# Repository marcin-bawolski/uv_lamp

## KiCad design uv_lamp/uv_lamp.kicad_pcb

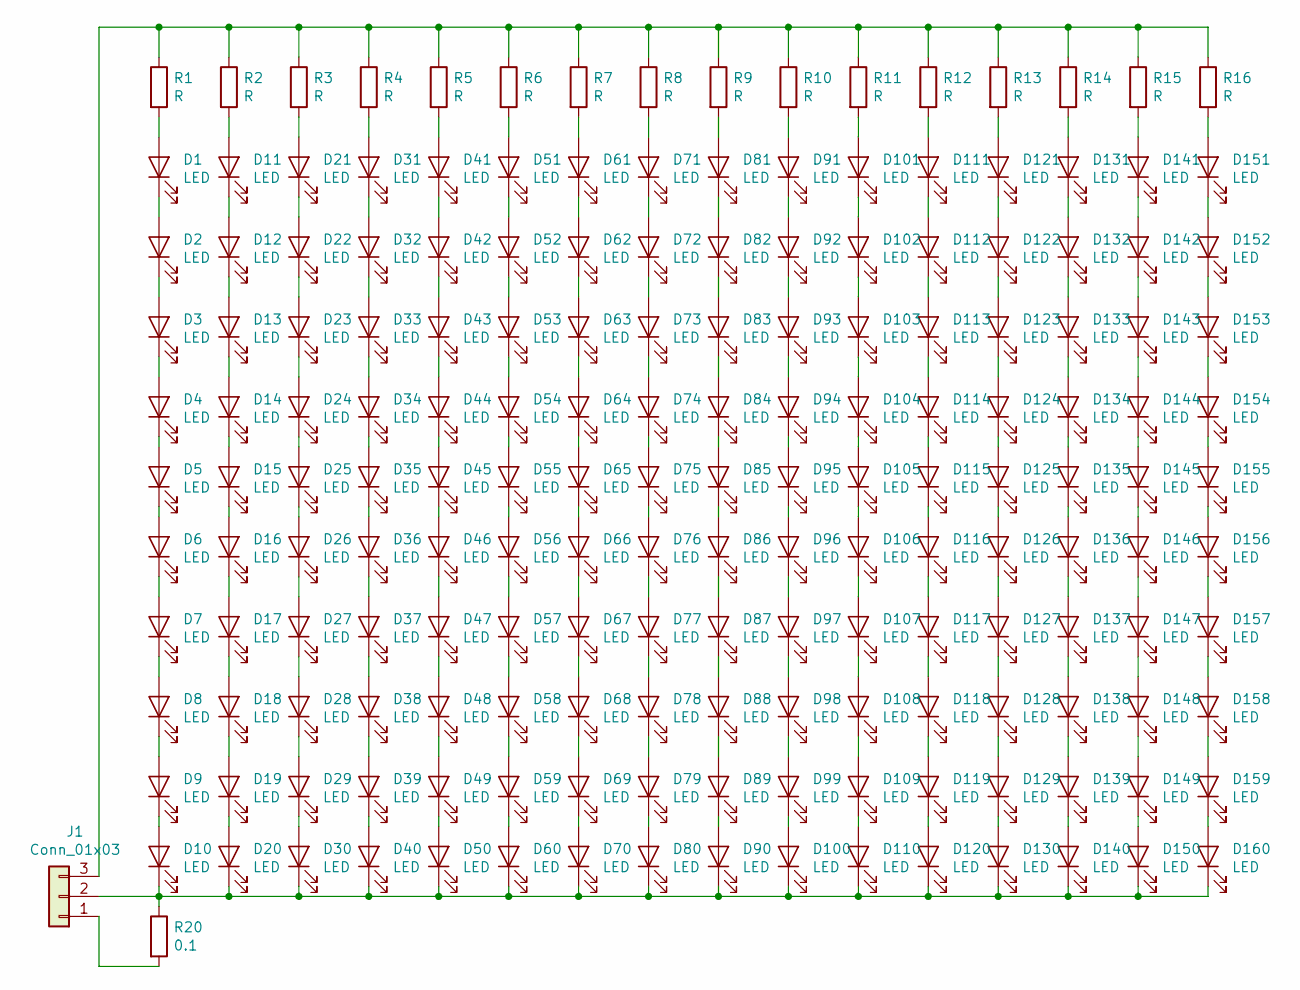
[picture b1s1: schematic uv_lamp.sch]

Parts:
D1, D2, D3, D4, D5, D6, D7, D8, D9, D10, D11, D12, D13, D14, D15, D16, D17, D18, D19, D20, D21, D22, D23, D24, D25, D26, D27, D28, D29, D30, D31, D32, D33, D34, D35, D36, D37, D38, D39, D40, D41, D42, D43, D44, D45, D46, D47, D48, D49, D50, D51, D52, D53, D54, D55, D56, D57, D58, D59, D60, D61, D62, D63, D64, D65, D66, D67, D68, D69, D70, D71, D72, D73, D74, D75, D76, D77, D78, D79, D80, D81, D82, D83, D84, D85, D86, D87, D88, D89, D90, D91, D92, D93, D94, D95, D96, D97, D98, D99, D100, D101, D102, D103, D104, D105, D106, D107, D108, D109, D110, D111, D112, D113, D114, D115, D116, D117, D118, D119, D120, D121, D122, D123, D124, D125, D126, D127, D128, D129, D130, D131, D132, D133, D134, D135, D136, D137, D138, D139, D140, D141, D142, D143, D144, D145, D146, D147, D148, D149, D150, D151, D152, D153, D154, D155, D156, D157, D158, D159, D160: LED; LED_D3.0mm_FlatTop
J1: Conn_01x03; JST_EH_S03B-EH_1x03_P2.50mm_Horizontal
R1, R2, R3, R4, R5, R6, R7, R8, R9, R10, R11, R12, R13, R14, R15, R16: R; R_0805_2012Metric_Pad1.15x1.40mm_HandSolder
R20: 0.1; R_1206_3216Metric_Pad1.42x1.75mm_HandSolder

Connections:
unnamed: D1.1 (K), D2.2 (A)
unnamed: D1.2 (A), R1.2
unnamed: D2.1 (K), D3.2 (A)
unnamed: D3.1 (K), D4.2 (A)
unnamed: D4.1 (K), D5.2 (A)
unnamed: D5.1 (K), D6.2 (A)
unnamed: D6.1 (K), D7.2 (A)
unnamed: D7.1 (K), D8.2 (A)
unnamed: D8.1 (K), D9.2 (A)
unnamed: D10.1 (K), D20.1 (K), D30.1 (K), D40.1 (K), D50.1 (K), D60.1 (K), D70.1 (K), D80.1 (K), D90.1 (K), D100.1 (K), D110.1 (K), D120.1 (K), D130.1 (K), D140.1 (K), D150.1 (K), D160.1 (K), J1.2, R20.1
unnamed: D9.1 (K), D10.2 (A)
unnamed: D11.1 (K), D12.2 (A)
unnamed: D11.2 (A), R2.2
unnamed: D12.1 (K), D13.2 (A)
unnamed: D13.1 (K), D14.2 (A)
unnamed: D14.1 (K), D15.2 (A)
unnamed: D15.1 (K), D16.2 (A)
unnamed: D16.1 (K), D17.2 (A)
unnamed: D17.1 (K), D18.2 (A)
unnamed: D18.1 (K), D19.2 (A)
unnamed: D19.1 (K), D20.2 (A)
unnamed: D21.1 (K), D22.2 (A)
unnamed: D21.2 (A), R3.2
unnamed: D22.1 (K), D23.2 (A)
unnamed: D23.1 (K), D24.2 (A)
unnamed: D24.1 (K), D25.2 (A)
unnamed: D25.1 (K), D26.2 (A)
unnamed: D26.1 (K), D27.2 (A)
unnamed: D27.1 (K), D28.2 (A)
unnamed: D28.1 (K), D29.2 (A)
unnamed: D29.1 (K), D30.2 (A)
unnamed: D31.1 (K), D32.2 (A)
unnamed: D31.2 (A), R4.2
unnamed: D32.1 (K), D33.2 (A)
unnamed: D33.1 (K), D34.2 (A)
unnamed: D34.1 (K), D35.2 (A)
unnamed: D35.1 (K), D36.2 (A)
unnamed: D36.1 (K), D37.2 (A)
unnamed: D37.1 (K), D38.2 (A)
unnamed: D38.1 (K), D39.2 (A)
unnamed: D39.1 (K), D40.2 (A)
unnamed: D41.1 (K), D42.2 (A)
unnamed: D41.2 (A), R5.2
unnamed: D42.1 (K), D43.2 (A)
unnamed: D43.1 (K), D44.2 (A)
unnamed: D44.1 (K), D45.2 (A)
unnamed: D45.1 (K), D46.2 (A)
unnamed: D46.1 (K), D47.2 (A)
unnamed: D47.1 (K), D48.2 (A)
unnamed: D48.1 (K), D49.2 (A)
unnamed: D49.1 (K), D50.2 (A)
unnamed: D51.1 (K), D52.2 (A)
unnamed: D51.2 (A), R6.2
unnamed: D52.1 (K), D53.2 (A)
unnamed: D53.1 (K), D54.2 (A)
unnamed: D54.1 (K), D55.2 (A)
unnamed: D55.1 (K), D56.2 (A)
unnamed: D56.1 (K), D57.2 (A)
unnamed: D57.1 (K), D58.2 (A)
unnamed: D58.1 (K), D59.2 (A)
unnamed: D59.1 (K), D60.2 (A)
unnamed: D61.1 (K), D62.2 (A)
unnamed: D61.2 (A), R7.2
unnamed: D62.1 (K), D63.2 (A)
unnamed: D63.1 (K), D64.2 (A)
unnamed: D64.1 (K), D65.2 (A)
unnamed: D65.1 (K), D66.2 (A)
unnamed: D66.1 (K), D67.2 (A)
unnamed: D67.1 (K), D68.2 (A)
unnamed: D68.1 (K), D69.2 (A)
unnamed: D69.1 (K), D70.2 (A)
unnamed: D71.1 (K), D72.2 (A)
unnamed: D71.2 (A), R8.2
unnamed: D72.1 (K), D73.2 (A)
unnamed: D73.1 (K), D74.2 (A)
unnamed: D74.1 (K), D75.2 (A)
unnamed: D75.1 (K), D76.2 (A)
unnamed: D76.1 (K), D77.2 (A)
unnamed: D77.1 (K), D78.2 (A)
unnamed: D78.1 (K), D79.2 (A)
unnamed: D79.1 (K), D80.2 (A)
unnamed: D81.1 (K), D82.2 (A)
unnamed: D81.2 (A), R9.2
unnamed: D82.1 (K), D83.2 (A)
unnamed: D83.1 (K), D84.2 (A)
unnamed: D84.1 (K), D85.2 (A)
unnamed: D85.1 (K), D86.2 (A)
unnamed: D86.1 (K), D87.2 (A)
unnamed: D87.1 (K), D88.2 (A)
unnamed: D88.1 (K), D89.2 (A)
unnamed: D89.1 (K), D90.2 (A)
unnamed: D91.1 (K), D92.2 (A)
unnamed: D91.2 (A), R10.2
unnamed: D92.1 (K), D93.2 (A)
unnamed: D93.1 (K), D94.2 (A)
unnamed: D94.1 (K), D95.2 (A)
unnamed: D95.1 (K), D96.2 (A)
unnamed: D96.1 (K), D97.2 (A)
unnamed: D97.1 (K), D98.2 (A)
unnamed: D98.1 (K), D99.2 (A)
unnamed: D99.1 (K), D100.2 (A)
unnamed: D101.1 (K), D102.2 (A)
unnamed: D101.2 (A), R11.2
unnamed: D102.1 (K), D103.2 (A)
unnamed: D103.1 (K), D104.2 (A)
unnamed: D104.1 (K), D105.2 (A)
unnamed: D105.1 (K), D106.2 (A)
unnamed: D106.1 (K), D107.2 (A)
unnamed: D107.1 (K), D108.2 (A)
unnamed: D108.1 (K), D109.2 (A)
unnamed: D109.1 (K), D110.2 (A)
unnamed: D111.1 (K), D112.2 (A)
unnamed: D111.2 (A), R12.2
unnamed: D112.1 (K), D113.2 (A)
unnamed: D113.1 (K), D114.2 (A)
unnamed: D114.1 (K), D115.2 (A)
unnamed: D115.1 (K), D116.2 (A)
unnamed: D116.1 (K), D117.2 (A)
unnamed: D117.1 (K), D118.2 (A)
unnamed: D118.1 (K), D119.2 (A)
unnamed: D119.1 (K), D120.2 (A)
unnamed: D121.1 (K), D122.2 (A)
unnamed: D121.2 (A), R13.2
unnamed: D122.1 (K), D123.2 (A)
unnamed: D123.1 (K), D124.2 (A)
unnamed: D124.1 (K), D125.2 (A)
unnamed: D125.1 (K), D126.2 (A)
unnamed: D126.1 (K), D127.2 (A)
unnamed: D127.1 (K), D128.2 (A)
unnamed: D128.1 (K), D129.2 (A)
unnamed: D129.1 (K), D130.2 (A)
unnamed: D131.1 (K), D132.2 (A)
unnamed: D131.2 (A), R14.2
unnamed: D132.1 (K), D133.2 (A)
unnamed: D133.1 (K), D134.2 (A)
unnamed: D134.1 (K), D135.2 (A)
unnamed: D135.1 (K), D136.2 (A)
unnamed: D136.1 (K), D137.2 (A)
unnamed: D137.1 (K), D138.2 (A)
unnamed: D138.1 (K), D139.2 (A)
unnamed: D139.1 (K), D140.2 (A)
unnamed: D141.1 (K), D142.2 (A)
unnamed: D141.2 (A), R15.2
unnamed: D142.1 (K), D143.2 (A)
unnamed: D143.1 (K), D144.2 (A)
unnamed: D144.1 (K), D145.2 (A)
unnamed: D145.1 (K), D146.2 (A)
unnamed: D146.1 (K), D147.2 (A)
unnamed: D147.1 (K), D148.2 (A)
unnamed: D148.1 (K), D149.2 (A)
unnamed: D149.1 (K), D150.2 (A)
unnamed: D151.1 (K), D152.2 (A)
unnamed: D151.2 (A), R16.2
unnamed: D152.1 (K), D153.2 (A)
unnamed: D153.1 (K), D154.2 (A)
unnamed: D154.1 (K), D155.2 (A)
unnamed: D155.1 (K), D156.2 (A)
unnamed: D156.1 (K), D157.2 (A)
unnamed: D157.1 (K), D158.2 (A)
unnamed: D158.1 (K), D159.2 (A)
unnamed: D159.1 (K), D160.2 (A)
unnamed: J1.1, R20.2
unnamed: J1.3, R1.1, R2.1, R3.1, R4.1, R5.1, R6.1, R7.1, R8.1, R9.1, R10.1, R11.1, R12.1, R13.1, R14.1, R15.1, R16.1

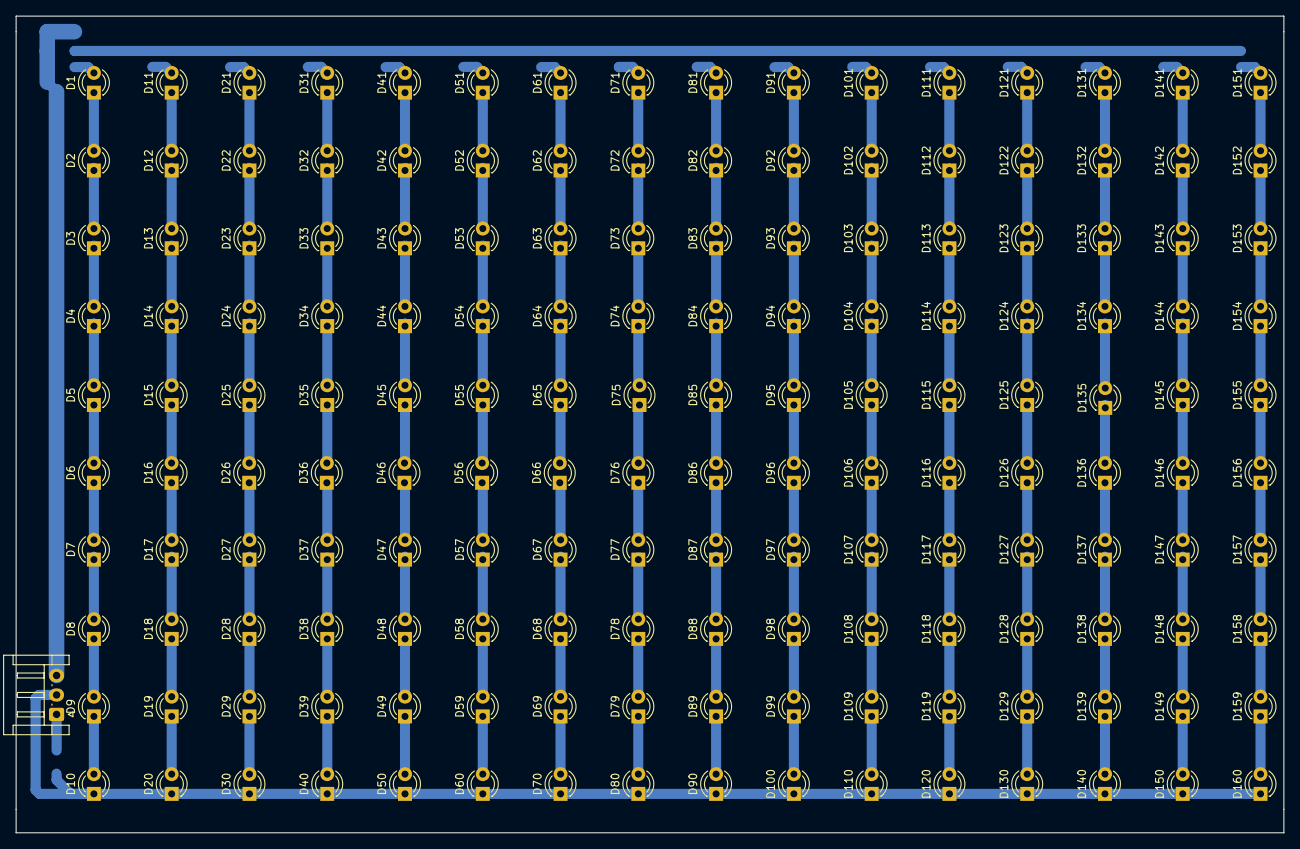
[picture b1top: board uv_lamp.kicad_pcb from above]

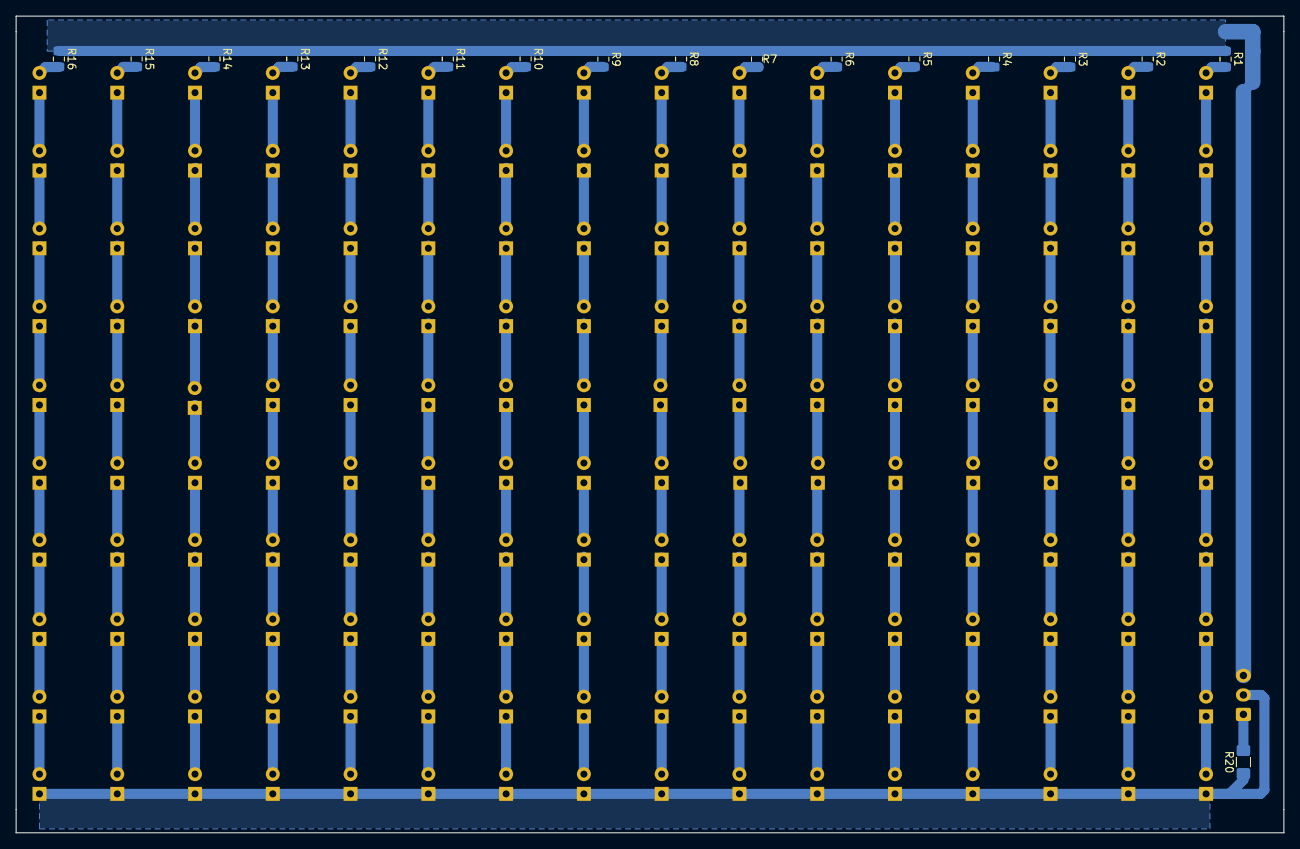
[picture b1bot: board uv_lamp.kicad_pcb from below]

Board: 2 copper layers, 163.0 x 105.0 mm, 178 parts (17 on the bottom side), 163 nets.

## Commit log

2020-04-04 Grid 7.25mm
2020-04-04 Grox 152x100mm
2020-04-04 Power bars
2020-04-04 DRC clean
2020-04-06 10mm led distance
